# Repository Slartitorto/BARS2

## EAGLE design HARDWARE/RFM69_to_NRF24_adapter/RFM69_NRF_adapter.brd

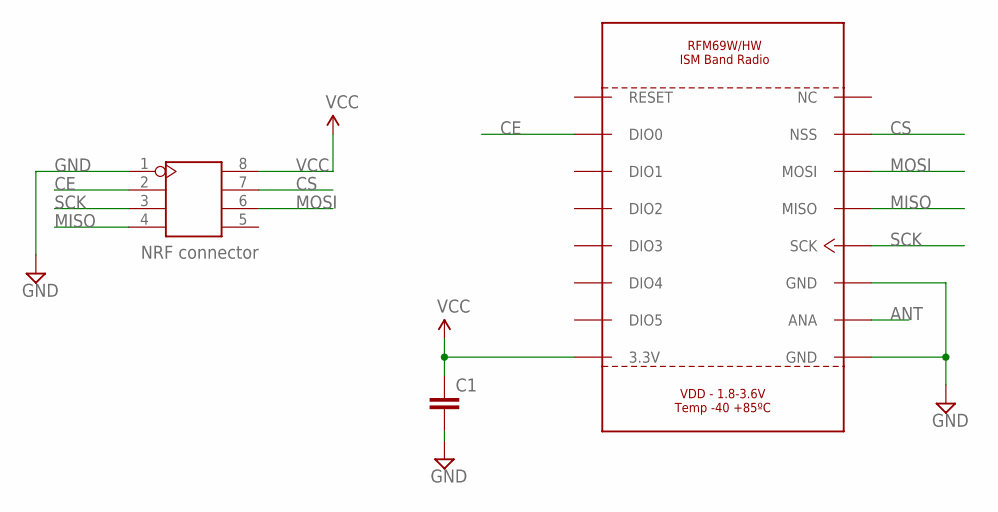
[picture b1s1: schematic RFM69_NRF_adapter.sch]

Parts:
C1: C-EUC1206K; C1206K
J1: NRF connector; 2X4P-2.54
U$1: RFM69W/HW-; RFM69W/HW

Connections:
ANT: U$1.P$10 (ANA)
CE: J1.2, U$1.P$2 (DIO0)
CS: J1.7, U$1.P$15 (NSS)
GND: C1.2, J1.1, U$1.P$9 (GND), U$1.P$11 (GND)
MISO: J1.4, U$1.P$13 (MISO)
MOSI: J1.6, U$1.P$14 (MOSI)
SCK: J1.3, U$1.P$12 (SCK)
VCC: C1.1, J1.8, U$1.P$8 (3.3V)

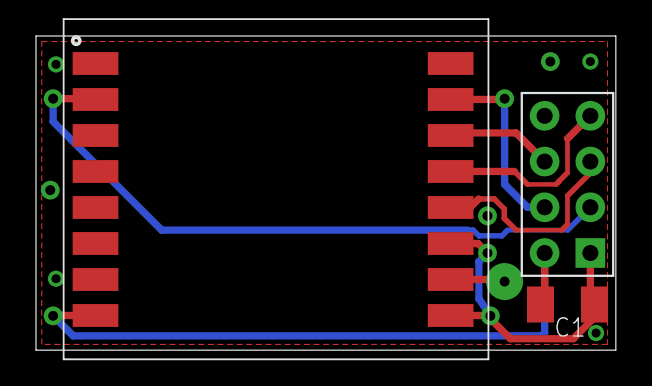
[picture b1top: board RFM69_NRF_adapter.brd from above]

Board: 2 copper layers, 32.2 x 17.5 mm, 3 parts (0 on the bottom side), 7 nets.

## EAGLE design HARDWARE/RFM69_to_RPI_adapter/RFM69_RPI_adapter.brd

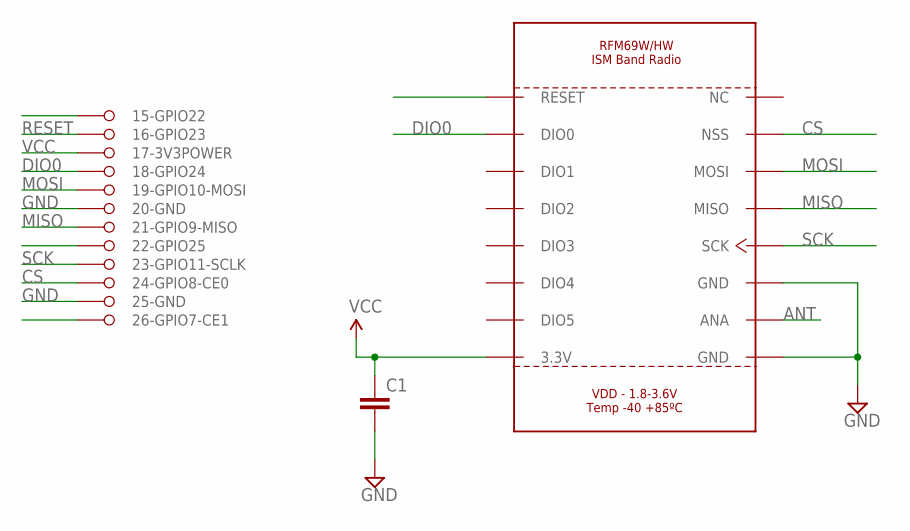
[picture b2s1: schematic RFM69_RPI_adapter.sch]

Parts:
C1: C-EUC1206K; C1206K
U$1: RFM69W/HW-; RFM69W/HW
U$2: RASPBPI_16-26; RASPBP1_16-26

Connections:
ANT: U$1.P$10 (ANA)
CS: U$1.P$15 (NSS), U$2.24-GPIO8-CE0
DIO0: U$1.P$2 (DIO0), U$2.18-GPIO24
GND: C1.2, U$1.P$9 (GND), U$1.P$11 (GND), U$2.20-GND, U$2.25-GND
MISO: U$1.P$13 (MISO), U$2.21-GPIO9-MISO
MOSI: U$1.P$14 (MOSI), U$2.19-GPIO10-MOSI
RESET: U$1.P$1 (RESET), U$2.16-GPIO23
SCK: U$1.P$12 (SCK), U$2.23-GPIO11-SCKL (23-GPIO11-SCLK)
VCC: C1.1, U$1.P$8 (3.3V), U$2.17-3V3POWER

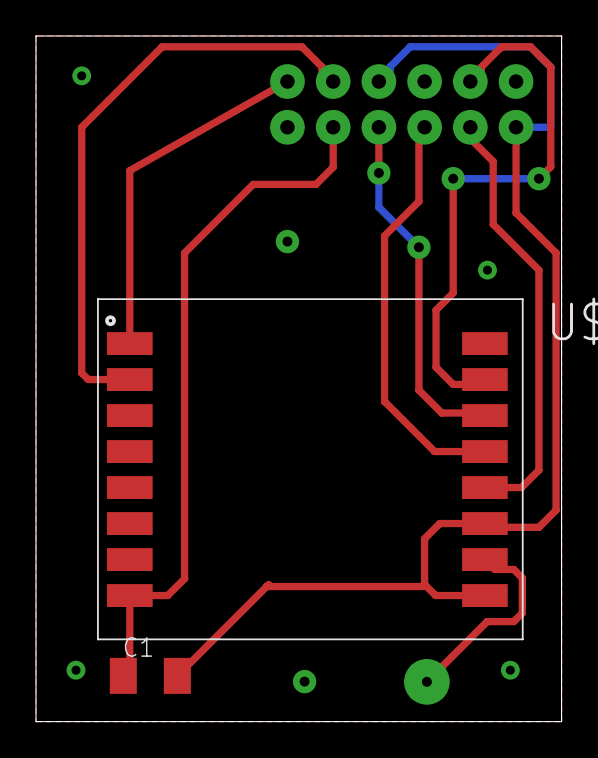
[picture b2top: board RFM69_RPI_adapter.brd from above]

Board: 2 copper layers, 29.2 x 38.1 mm, 3 parts (0 on the bottom side), 8 nets.

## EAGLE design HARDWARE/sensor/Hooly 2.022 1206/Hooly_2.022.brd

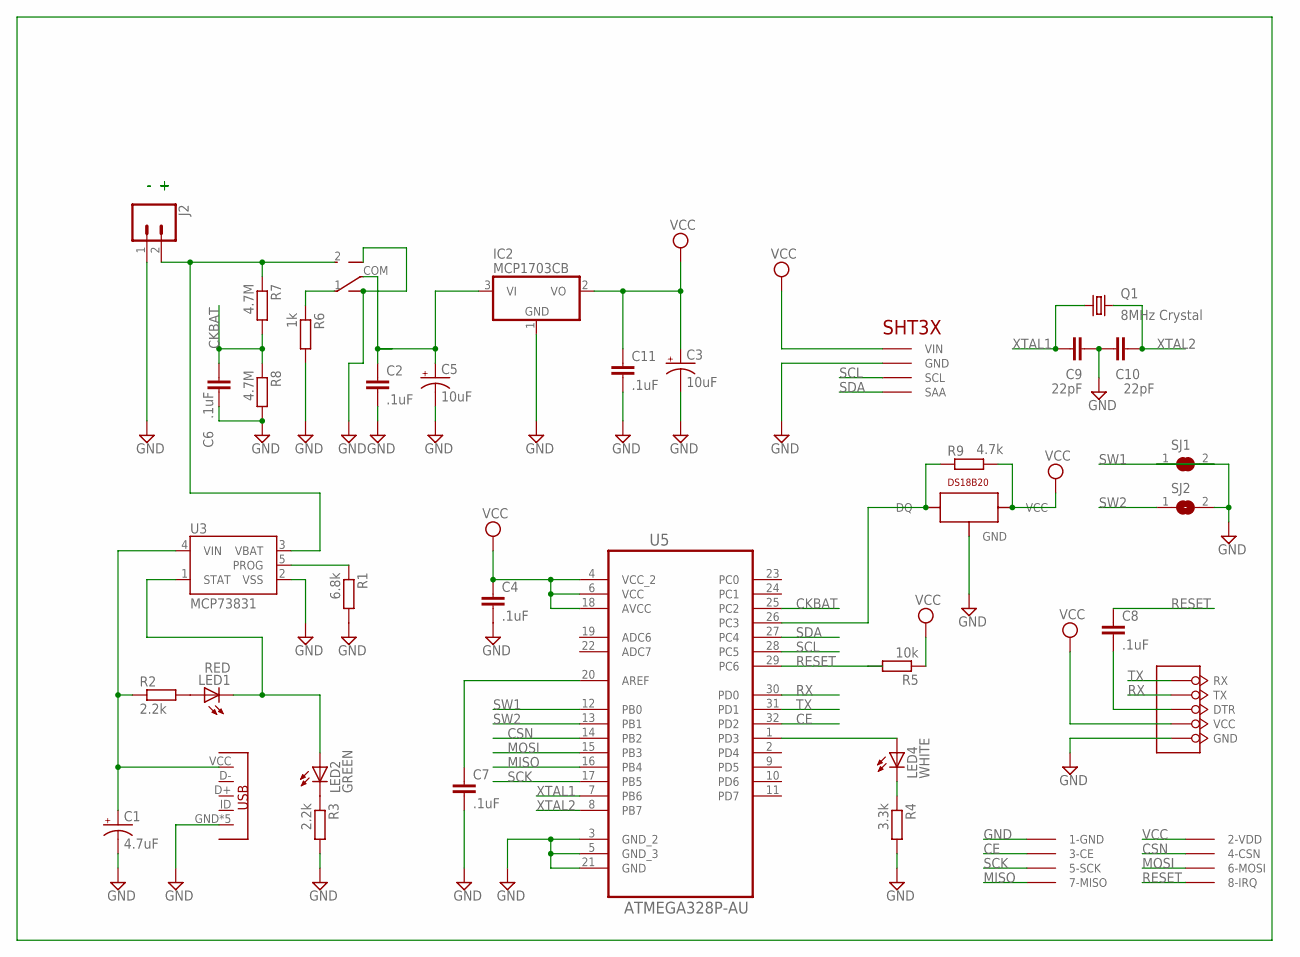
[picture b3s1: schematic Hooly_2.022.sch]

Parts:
C1: 4.7uF; CPOL-RADIAL-2.5MM-5MM
C2, C4, C6, C7, C8, C11: .1uF; C1206
C3, C5: 10uF; CPOL-RADIAL-2.5MM-5MM
C9, C10: 22pF; C0603K
IC2: MCP1703CB; SOT23
J2: CONN_02; 1X02
LED1: RED; CHIPLED_1206
LED2: GREEN; CHIPLED_1206
LED4: WHITE; CHIPLED_1206
Q1: 8MHz Crystal; 5.0X3.2_2
R1: 6.8k; R1206
R2, R3: 2.2k; R1206
R4: 3.3k; R1206
R5: 10k; R1206
R6: 1k; R1206
R7, R8: 4.7M; R1206
R9: 4.7k; R1206
SJ1, SJ2: SJ
U3: MCP73831; SOT23-5
U5: ATMEGA328P-AU; QFP80P900X900X120-32N
U$1: SHT3XLARGE; MYSHT3X
U$2: MYSWITCH2MM; MYSWITCH
U$3: MYDS18B20
U$4: MYNRF24L01SOCKET
U$6: FTDI232
U$7: MYMICROUSB

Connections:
CE: U5.32 (PD2), U$4.CE (3-CE)
CKBAT: C6.1, R7.2, R8.1, U5.25 (PC2)
CSN: U5.14 (PB2), U$4.CSN (4-CSN)
DTR: C8.2, U$6.DTR
GND: C1.2 (-), C2.2, C3.2 (-), C4.2, C5.2 (-), C6.2, C7.2, C9.2, C10.1, C11.2, IC2.1 (GND), J2.1, R1.2, R3.2, R4.2, R6.2, R8.2, SJ1.1, SJ2.2, U3.2 (VSS), U5.3 (GND_2), U5.5 (GND_3), U5.21 (GND), U$1.GND, U$2.GND1, U$2.GND2, U$3.GND, U$4.GND (1-GND), U$6.GND, U$7.GND, U$7.P$6 (GND), U$7.P$7 (GND), U$7.P$8 (GND), U$7.P$9 (GND)
MISO: U5.16 (PB4), U$4.MISO (7-MISO)
MOSI: U5.15 (PB3), U$4.MOSI (6-MOSI)
unnamed: C2.1, C5.1 (+), IC2.3 (VI), U$2.COM
unnamed: LED4.A, U5.1 (PD3)
unnamed: LED1.A, R2.2
unnamed: LED2.C, R3.1
unnamed: LED1.C, LED2.A, U3.1 (STAT)
unnamed: R6.1, U$2.1
unnamed: R1.1, U3.5 (PROG)
unnamed: C7.1, U5.20 (AREF)
unnamed: R9.1, U5.26 (PC3), U$3.DQ
unnamed: LED4.C, R4.1
RESET: C8.1, R5.2, U5.29 (PC6), U$4.IRQ (8-IRQ)
RX: U5.30 (PD0), U$6.TX
SCK: U5.17 (PB5), U$4.SCK (5-SCK)
SCL: U5.28 (PC5), U$1.SCL
SDA: U5.27 (PC4), U$1.SAA
SW1: SJ1.2, U5.12 (PB0)
SW2: SJ2.1, U5.13 (PB1)
TX: U5.31 (PD1), U$6.RX
VBATT: J2.2, R7.1, U3.3 (VBAT), U$2.2
VCC: C3.1 (+), C4.1, C11.1, IC2.2 (VO), R5.1, R9.2, U5.4 (VCC_2), U5.6 (VCC), U5.18 (AVCC), U$1.VIN, U$3.VCC, U$4.VDD (2-VDD), U$6.VCC
VUSB: C1.1 (+), R2.1, U3.4 (VIN), U$7.VCC
XTAL1: C9.1, Q1.1, U5.7 (PB6)
XTAL2: C10.2, Q1.2, U5.8 (PB7)

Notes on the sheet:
- +

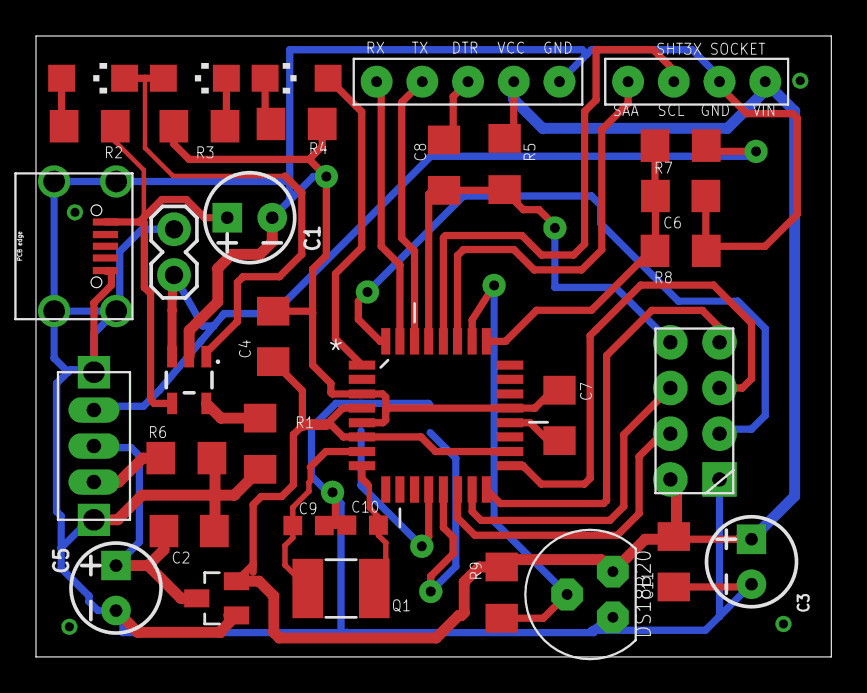
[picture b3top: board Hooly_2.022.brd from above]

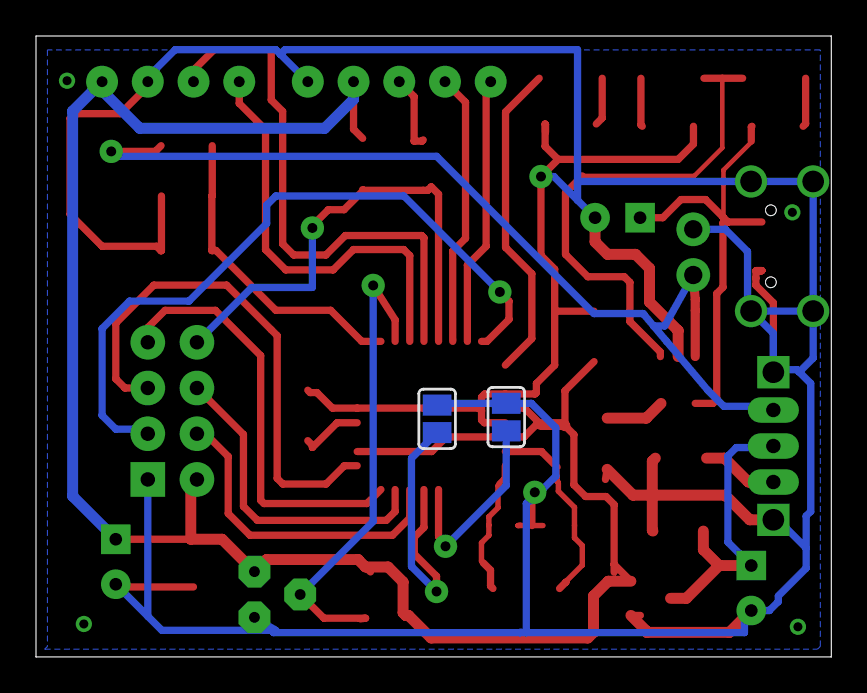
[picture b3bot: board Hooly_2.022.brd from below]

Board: 2 copper layers, 44.2 x 34.5 mm, 36 parts (2 on the bottom side), 30 nets.

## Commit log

2017-12-28 first release
2017-12-28 bug fixing & minor changes
2017-12-30 minor changes
2017-12-31 Defined 575 as minimum battery level
2017-12-31 Adjusted min battery level
2017-12-31 100% battery params verified
2018-01-05 var counter long (int < 32768)
2018-01-06 DEBUG on vcc inside setup get_code_period string and not 00000
2018-01-06 Done code_period_setup
2018-01-06 done get_code_period
2018-01-06 Maybe there is a bug in sprintf
2018-01-10 Minor changes (comments)
2018-01-10 Added hardware schema and board
2018-01-10 removed not used file
2018-01-27 Last commit was in error. Add RSSI on link quality
2018-01-27 At get_code_period statement, doesn’t send zero data on server
2018-01-27 DEBUG_PERIOD definition
2018-03-09 Hardware update
2018-03-09 Web update
2018-03-09 Moved from WEB directory for better use of git
2018-03-09 Only file permissions
2018-03-09 added useful db cretentials
2018-03-29 general revision
2018-03-30 bug fixed
2018-03-30 query tuned
2018-03-31 Report fine
2018-03-31 Last report
2018-04-06 data_type field removed
2018-04-06 print pdf table in landscape with grid
2018-04-08 Nothing
2018-04-08 Modified command “gn” for code period request
2018-04-08 new firmware with code_period setup at startup - Tested with RFM69HW and raspberry receiver
2018-04-10 firmware aggiornato con code_period setup
2018-04-14 General revision - tested
2018-04-14 Added for delete cookies and login again
2018-04-14 Led signals on get period command
2018-04-17 tables adjustment
2018-04-19 POST method instead of GET
2018-04-19 now use POST method manage last and serial from select list
2018-04-21 rename cookie_delete
2018-04-21 change Hooly in MyHooly
2018-04-21 Add column on DB for safe change password with token
2018-04-21 login, registration, change password etc, in html5 with new css
2018-04-21 add sliding for advanced preferences
2018-04-21 some adjustments
2018-04-21 some adjustment
2018-04-21 graphics adjustment
2018-04-22 Other adjustments
2018-04-24 auto t0 = 1 per demo
2018-04-29 none
2018-05-05 Other
2018-05-24 rilevazioni manuali
2018-05-24 Inserita registrazione manuale
2018-05-24 Gestione rilevazioni manuali fase 1
2018-05-28 Gestione rilevazioni manuali
2018-05-28 finita modifica RM
2018-05-30 cookie alert
2018-06-02 Repeater
2018-06-03 Multichannel notification and different battery types
2018-08-20 add sms notify method
2018-08-31 Add icona
2018-08-31 add sms alert to router_alive_check.cpp and other
2018-09-02 Added logfile
2018-09-02 Other on log file
2018-09-02 Valori batteria e RSS in rosso se sotto soglia
2018-09-02 risolti errori nei log a causa di una variable non settata (code_period)
2018-09-02 Abilitato flag per notifica sms
2018-09-05 Repeater quasi pronto
2018-09-10 altro
2018-09-11 Receiver (hooly-router) 0.3 add repeater info in url add delay(200) before and (100) after the echo to be repeater well working
2018-09-11 Repeater v. 0.2
2018-09-11 Repeater vers. 0.3 Tested
2018-09-11 Add repeater variable in get
2018-09-11 Add user info in table sa04
2018-09-11 Add redirection when user without router Review icons and warning messages
2018-09-11 Add new router management by new user
2018-09-11 Add pin filed in new_router queries
2018-09-24 Bug fixing
2018-09-24 settings limits min and max to max and min
2018-09-27 add delete_devices function
2018-10-07 hooly_firmware 2.05
2018-10-11 Add checksum
2018-11-14 Add data trash
2018-11-15 Add billing info
2018-11-16 Gestione apici e doppi apici in info personali e billing
2018-11-17 removed CURRENT_TIMESTAMP ON UPDATE CURRENT_TIMESTAMP from rec_data
2018-11-18 Add sendmessage. It get params from db and serves for datasink
2018-11-18 version description
2018-11-25 New version working and with configuration file
2018-11-25 Arrows images for datepicker
2018-12-01 Manage sms
2018-12-01 Paypal button for sms
2018-12-01 sms table improvement
2018-12-06 new version with bug fixing. Use send message.php with codUtente in order to decrease sms credit
2018-12-08 WiFiManager.h settings
2018-12-09 add checksum control
2018-12-10 rimossa distinzione tra data_sink e data_sink_check. Adesso va tutto su data_sink, anche i router con checksum
2018-12-14 testo in grigio
2018-12-14 bug fixing (mail di attivazione nuova password)
2018-12-15 1) possibilità di aggiungere un router 2) gestione conto mensile e credito
2018-12-15 Bug fixing: colore link errato nel menu
2018-12-15 Menu a tre livelli e razionalizzazione delle voci
2018-12-15 Eliminati dettagli dalla pagina device_details ed inseriti in pop-up
2018-12-15 Non stampa i menu nella pagina device_details
2018-12-16 Tabella info su device_detail su una colonna e aggiunte altre informazioni
2018-12-16 Aggiunto link PayPal per accreditare importi, con cod_utente; aggiunto cod_utente al pagamento PayPal per gli sms
2018-12-16 Ricarica servizio con PayPal in finestra modal
2018-12-16 aggiustamenti minori
2018-12-17 Modal PayPal nella sezione di ricarica SMS uniformato alla sezione ricarica servizio
2018-12-17 nella tabella di utilizzo del credito importi a credito in verde, a debito in rosso; aggiornata tabella (nuovo campo cred_deb)
2018-12-21 Piccoli aggiustamenti grafici e Logout nel menu Account
2018-12-21 Elaborazione device_details con modal per impostazioni ed export dati
2018-12-22 Aggiunto css per tabelle con righe (per crediti sms e servizio). Inseriti <thead> e <tbody> Modificato generals per usare le tabelle rowed
2018-12-24 Eliminata icona grafico per i dettagli (device_details); ora il link è sul nome del sensore. Sistemata la posizione del tooltip
2018-12-25 Primi aggiustamenti per RWD
2018-12-25 Aggiustamenti per RWD
2019-03-15 Update stile.css
    minor changes

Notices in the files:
parts and their libraries:
SparkFun-Capacitors: Licensing: Creative Commons ShareAlike 4.0 International - https://creativecommons.org/licenses/by-sa/4.0
crystal-geyer_V1_0: Copyright: Geyer-Electronic
